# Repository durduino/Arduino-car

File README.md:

# Arduino-car
Bluetooth controlled Arduino car

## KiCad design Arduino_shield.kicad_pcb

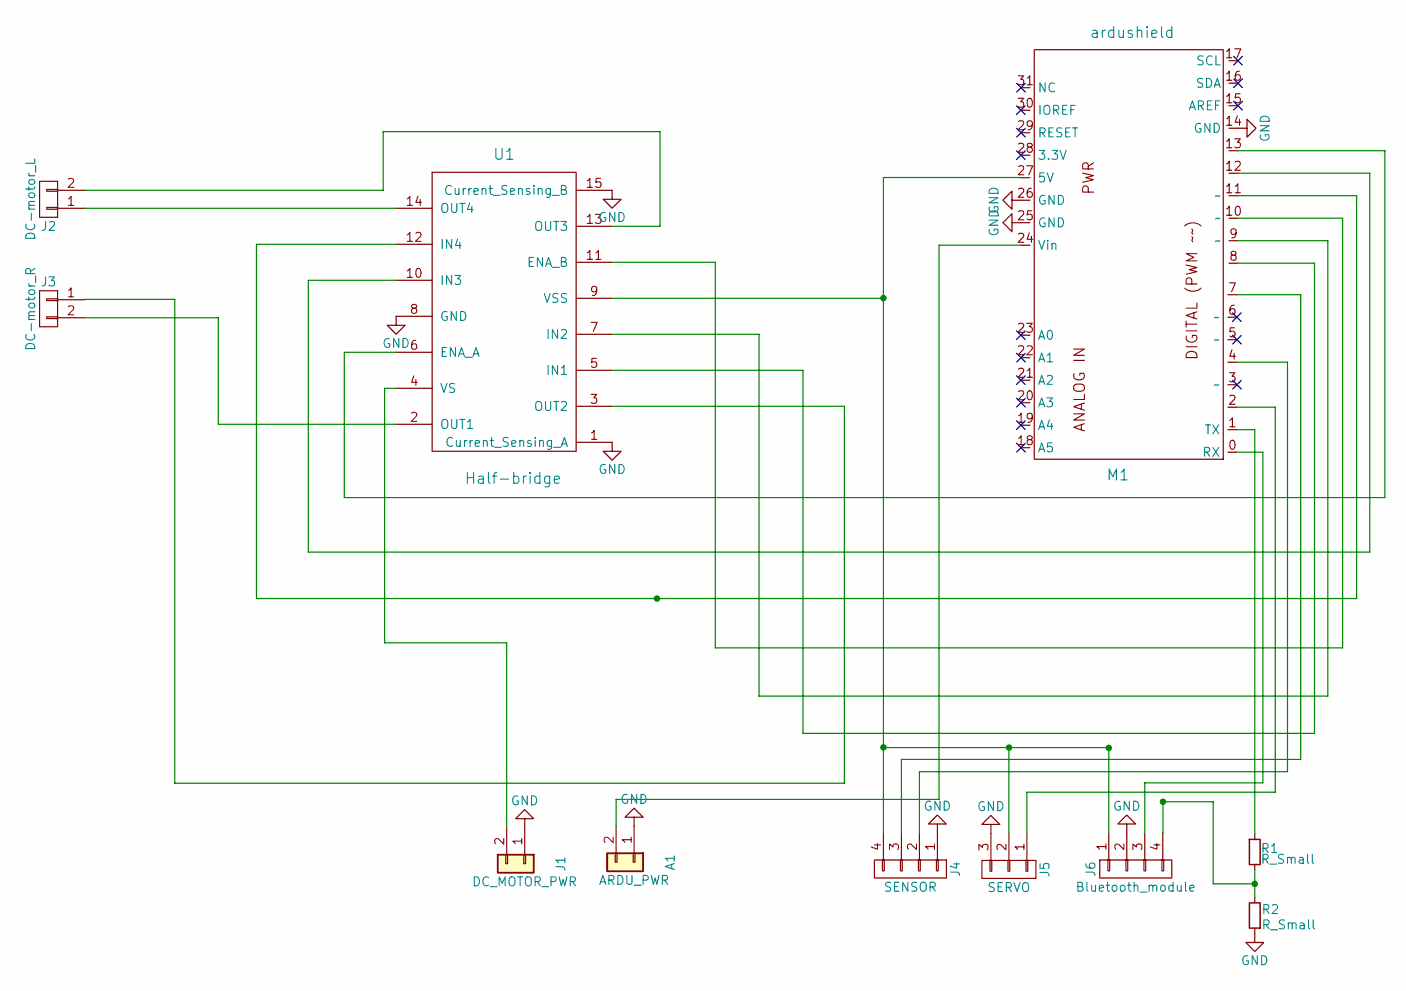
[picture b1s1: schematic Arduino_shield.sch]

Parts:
A1: ARDU_PWR; Pin_Header_Angled_1x02_Pitch2.54mm
J1: DC_MOTOR_PWR; Pin_Header_Angled_1x02_Pitch2.54mm
J2: DC-motor_L; Pin_Header_Angled_1x02_Pitch2.54mm
J3: DC-motor_R; Pin_Header_Angled_1x02_Pitch2.54mm
J4: SENSOR; Pin_Header_Angled_1x04_Pitch2.54mm
J5: SERVO; Pin_Header_Angled_1x03_Pitch2.54mm
J6: Bluetooth_module; Pin_Header_Angled_1x04_Pitch2.54mm
M1: ardushield; Ardushield
R1, R2: R_Small; Pin_Header_Angled_1x02_Pitch2.54mm
U1: Half-bridge

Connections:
GND: A1.1, J1.1, J4.1, J5.3, J6.2, M1.14 (GND), M1.25 (GND), M1.26 (GND), R2.1, U1.1 (Current_Sensing_A), U1.8 (GND), U1.15 (Current_Sensing_B)
unnamed: A1.2, M1.24 (Vin)
unnamed: J1.2, U1.4 (VS)
unnamed: J2.1, U1.14 (OUT4)
unnamed: J2.2, U1.13 (OUT3)
unnamed: J3.1, U1.3 (OUT2)
unnamed: J3.2, U1.2 (OUT1)
unnamed: J4.2, M1.4
unnamed: J4.3, M1.7
unnamed: J4.4, J5.2, J6.1, M1.27 (5V), U1.9 (VSS)
unnamed: J5.1, M1.2
unnamed: J6.3, M1.0 (RX)
unnamed: J6.4, R1.2, R2.2
unnamed: M1.1 (TX), R1.1
unnamed: M1.8, U1.5 (IN1)
unnamed: M1.9 (~~), U1.7 (IN2)
unnamed: M1.10 (~~), U1.11 (ENA_B)
unnamed: M1.11 (~~), U1.12 (IN4)
unnamed: M1.12, U1.10 (IN3)
unnamed: M1.13, U1.6 (ENA_A)

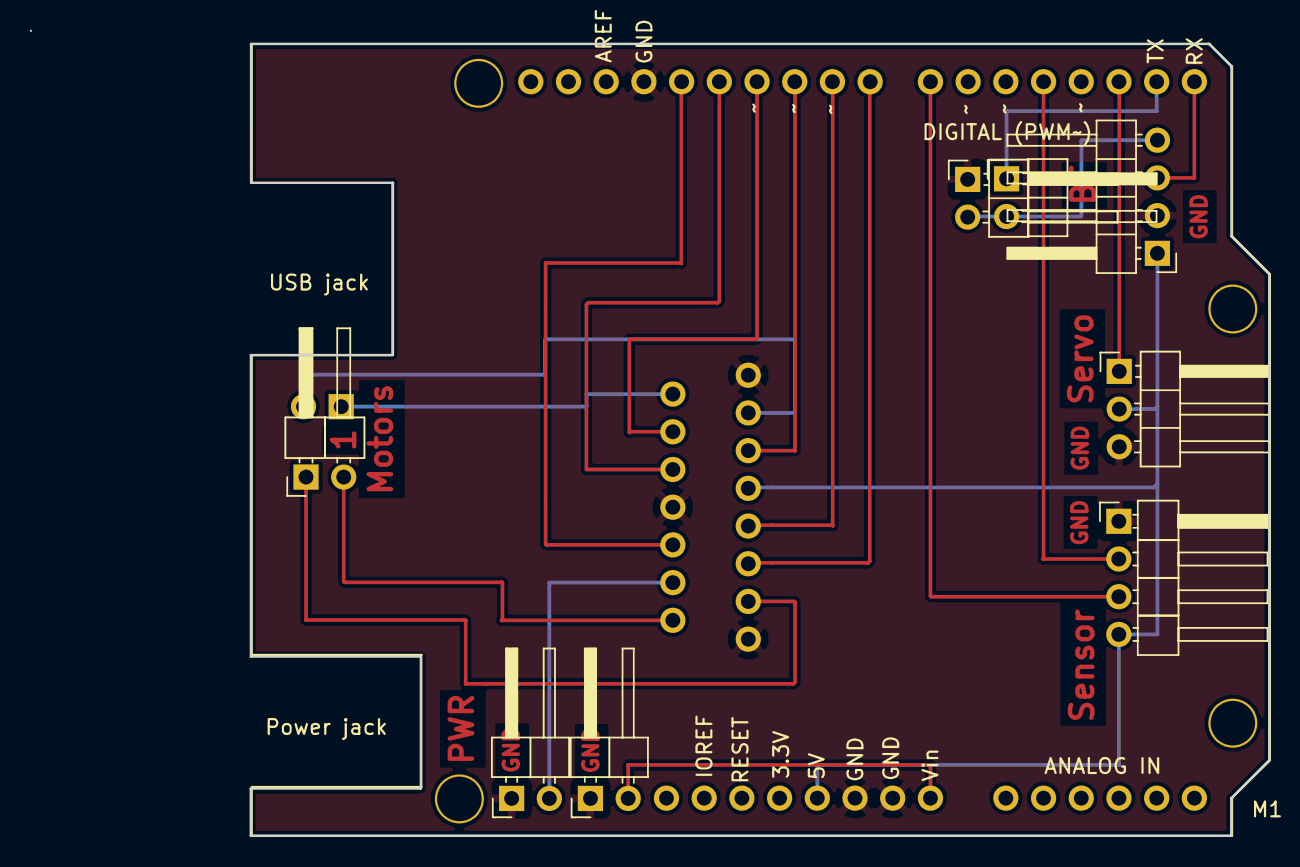
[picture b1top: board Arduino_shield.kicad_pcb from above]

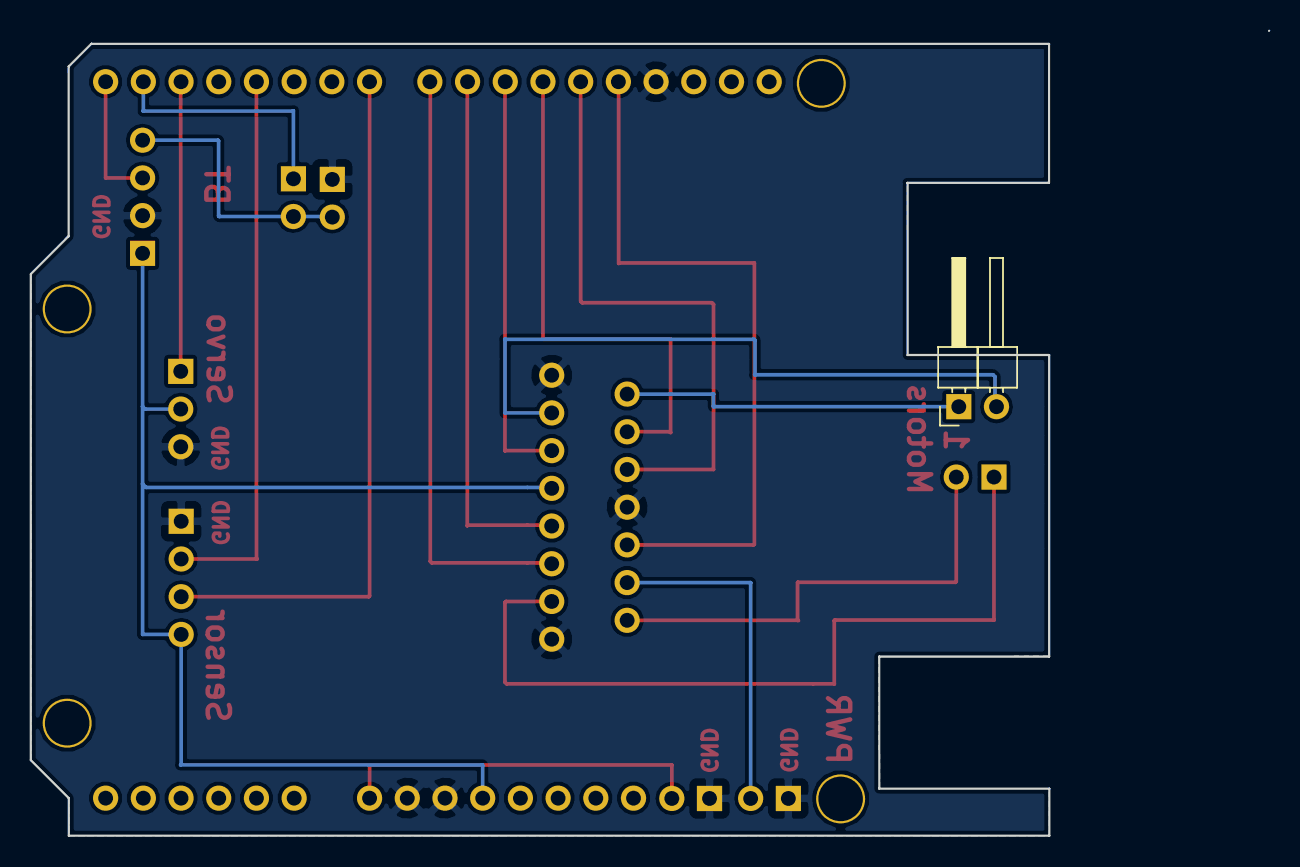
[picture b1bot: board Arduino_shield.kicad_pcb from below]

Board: 2 copper layers, 83.4 x 54.2 mm, 11 parts (2 on the bottom side), 20 nets.

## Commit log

2018-06-27 Add files via upload
    Arduino_shield PCB
